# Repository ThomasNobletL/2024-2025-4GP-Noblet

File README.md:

<h1 align = "center"> Projet Capteur Graphite 4A - GP <h1> 
<h2 align="center"> Par NOBLET Thomas </h2>
<h3 align="center"> INSA de Toulouse, département Génie Physique, année 2024 - 2025 </h3>
  
<p align="center">
  
</p>

## <h2 align = "center"> Mesure de contrainte sous arduino & python d'un capteur graphite <h1>

### 1. Description

*Contexte*

Le projet consiste à reproduire une technologie low-tech de capteur de flexion en graphite, se basant sur l'article "Pencil Drawn Strain Gauges and Chemiresistors on Paper" de Cheng-Wei Lin, Zhibo Zhao, Jaemyung Kim & Jiaxing Huang.

*Principe*

Des traces de crayons sur du papier se comportent comme des résistances dont la valeur varie en fonction de la courbure du papier sur lequel elles sont dessinées. 

*Contenu du projet*

Une [datasheet du capteur](05_DataSheet/Graphite_Sensor_DATA_SHEET.pdf) a pu être réalisée à l'aide d'une carte Arduino Uno, d'un circuit d'amplification (dont le PCB a été réalisé sur KICAD) et d'une interface python.

***Matériel utilisé (non exhaustif)***
- **Capteur de contrainte en graphite** : Mine HB conseillée
- **LTC1050** : Amplificateur du circuit 
- **MCP 41050** : Permet de faire varier le gain du circuit d'amplification
- **Module Bluetooth HC-05** : Récupérer les données en Bluetooth  
- **Ecran OLED SS1306 en I2C** : Affichage des données sur le PCB

### 2. Circuit d'amplification & PCB

Le circuit d'amplification utilise un amplificateur LTC1050 avec un gain de R2/R1. La résistance R1 est un potentiomètre MCP41050 (de 125Ω à 50kΩ) donnant une plage de gain de 2 à 800.

<p align="center"><em>Figure 1 : Schéma Amplification </em></p>

<p align="center"><em>Figure 2 : Circuit réel </em></p>

Le PCB utilisé est celui-ci, avec les pins Rx et Tx de l'arduino connectées au HC05 (PCB Incorrect). Cette configuration est utilisable si on souhaite uploader le code arduino directement en bluetooth, mais il faut impérativement utiliser les pins 2 et 3 pour un upload depuis le port USB. Les pins 0 et 1 sont également utilisées par la liaison série vers un PC, ce qui provoque des erreurs en utilisant la connexion bluetooth sur ce port.

<p align="center"><em>Figure 3 : PCB Incorrect </em></p>

En l'occurence, aucun des codes python et arduino fournis fonctionnera durablement avec le premier PCB (30s), une erreurs série arrivera relativement rapidement, le PCB a donc été modifié à l'aide de câble pour correspondre à ce nouveau PCB. 

<p align="center"><em>Figure 4 : PCB Corrigé</em></p>

### 3. Interface & code Python 

L'architecture du code est décrite si dessous. La valeur de la résistance ainsi que l'affichage des mesures se fait directement depuis l'interface Qt, qui communique avec un thread gérant l'acquisition et l'envoie de données vers l'arduino qui les réceptionnes. Le code fonctionne à la fois en liaison série et bluetooth, il suffit de choisir depuis "Port choice".

Une valeur du gain observé est affichée dans l'interface, mais ne permet que d'obtenir un ordre de grandeur, la sensibilité des mesures sur l'arduino étant de 4,88 mV et le signal d'entrée trop faible (d'où l'intérêt du circuit d'amplification).

<p align="center"><em>Figure 5 : Architecture du code</em></p>

<p align="center"><em>Figure 5 : Interface Qt</em></p>

Le "run" permet de lancer le stockage des données reçues, mais écrase la précédente série réalisée, il faut donc sauvegarder directement après la fin de l'acquisition si le but est de prendre plusieurs séries d'affilée. 

### 4. Résultats

Les mesures ont été effectuées à l'aide de cylindres de diamètre **D** de **2, 2.5, 3, 3.5, 4, 4.5 et 5 cm** ainsi que de crayons de mines HB, 2B et 4B.
Avec la déformation $\epsilon$ = e/D, e étant l'épaisseur du papier (0,1 mm).

<p align="center"><em>Graphique 1 : Réponse en compression</em></p>

<p align="center"><em>Graphique 2 : Réponse en détente</em></p>

On remarque que la variation de résistance en compression et en détente est plus importante pour une mine moyennement dure et grasse (HB) que pour des mines plus grasses (2B, 4B).

<p align="center"><em>Graphique 3 : Comparaison avec un Flex sensor  </em></p>

En comparant avec un flex sensor de Spectra Symbol, on remarque que la réponse en détente est assez cohérente avec celle du capteur en graphite produit (le flex sensor de Spectra Symbol ne permet pas de comparer en compression, [Datasheet](06_Other/FLEX_SENSOR_-_SPECIAL_EDITION_DATA_SHEET.pdf)). De plus, les mesures on étés prises sans utiliser le circuit d'amplification. 

### 5. Limites et perspectives

*Le Bluetooth du HC-05*

  La connexion entre le module HC-05 et un PC est **trop instable** pour utiliser seulement l'interface python fournie **sur Mac OS**, l'appairage échoue souvent ou se coupe régulièrement. Il est préférable d'utiliser une connexion avec un port série. 
  
*Utilisation d'un module Wifi ESP32*

  Remplacer le HC-O5 par un module Wifi ESP32 pourrait permettre de se connecter plus aisément avec les OS Mac sur un même réseau et également en bluetooth.

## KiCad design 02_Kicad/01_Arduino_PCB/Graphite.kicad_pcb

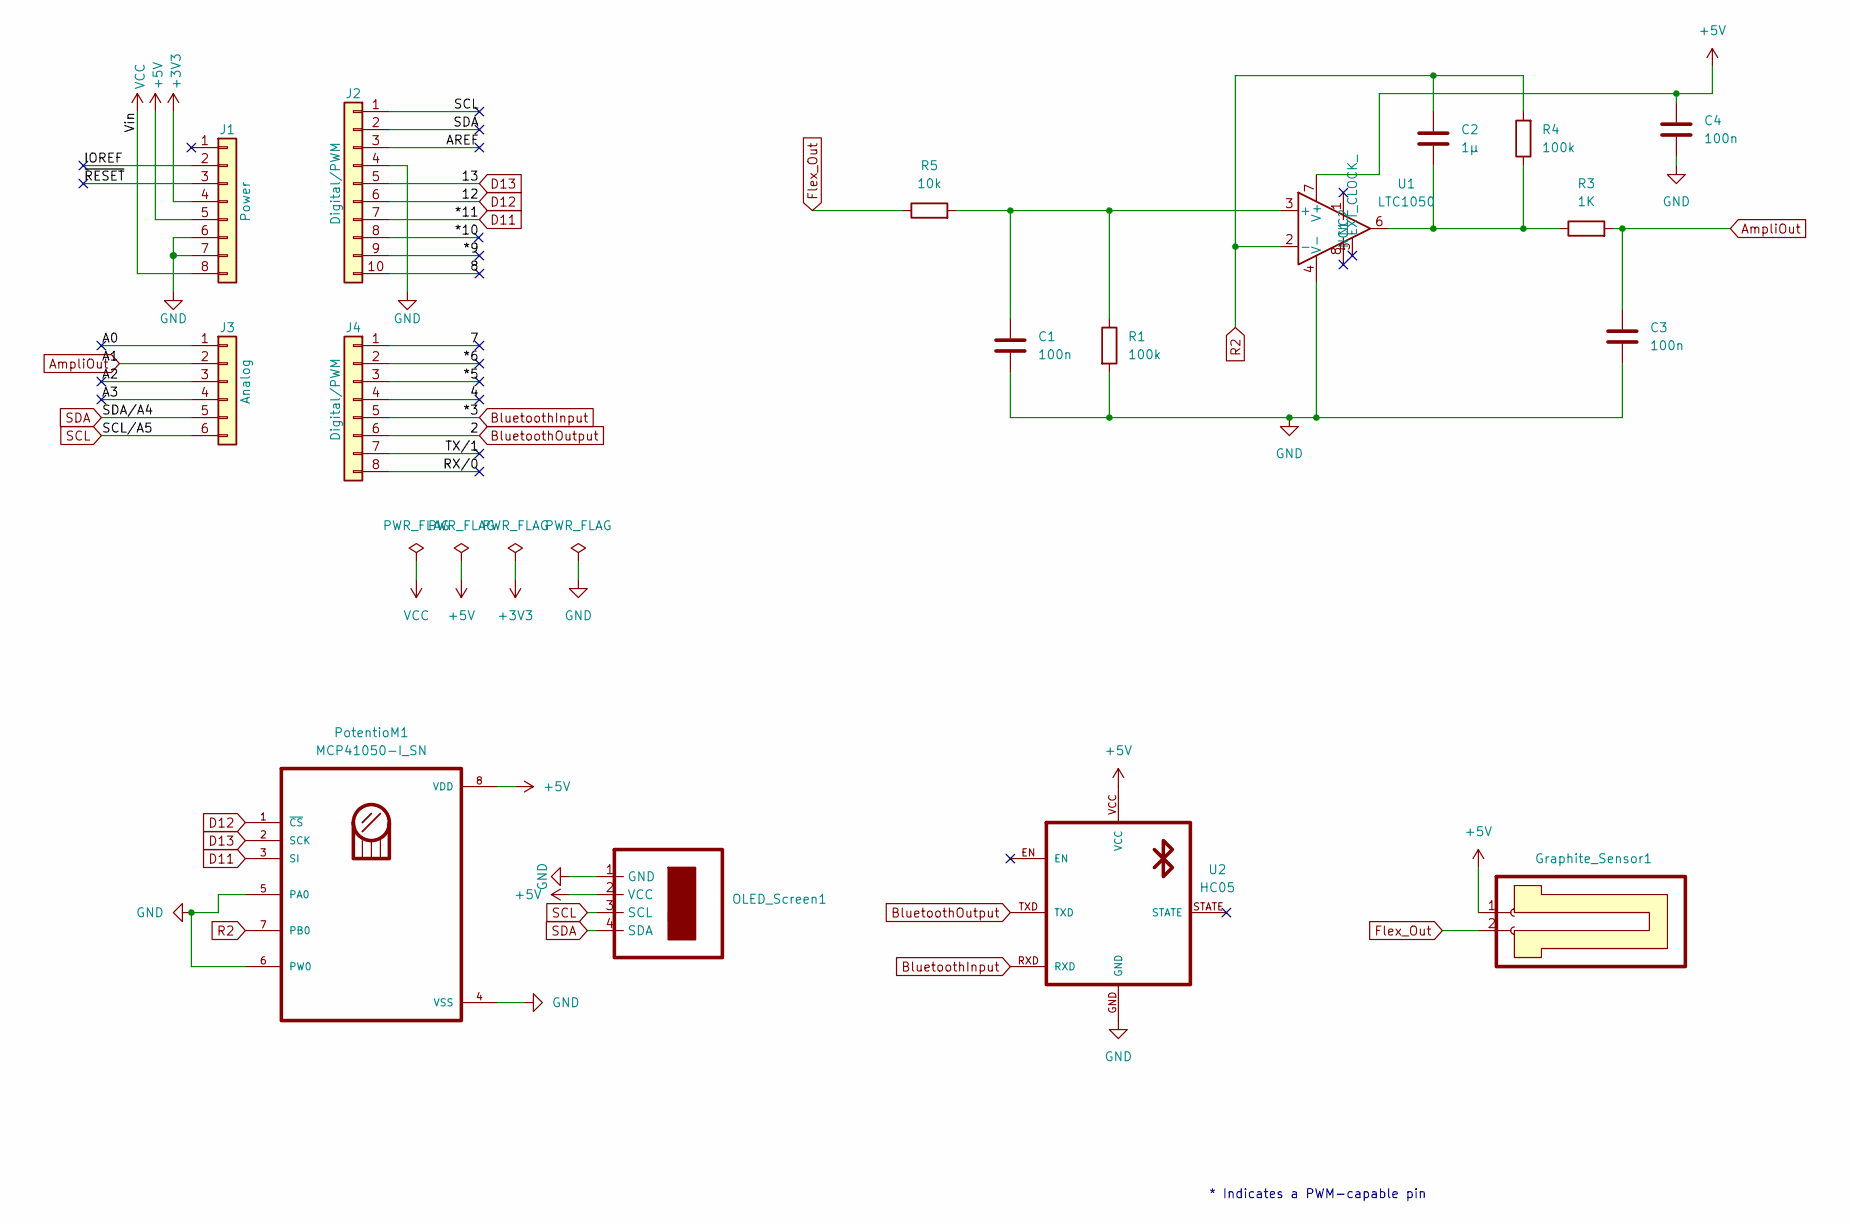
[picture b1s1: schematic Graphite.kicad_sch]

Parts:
C1, C3, C4: 100n; C_Disc_D3.0mm_W2.0mm_P2.50mm
C2: 1µ; C_Rect_L7.0mm_W4.5mm_P5.00mm
Graphite_Sensor1: Sensor
J1: Power; PinSocket_1x08_P2.54mm_Vertical
J2: Digital/PWM; PinSocket_1x10_P2.54mm_Vertical
J3: Analog; PinSocket_1x06_P2.54mm_Vertical
J4: Digital/PWM; PinSocket_1x08_P2.54mm_Vertical
OLED_Screen1: OLED
PotentioM1: MCP41050-I_SN; MCP41050
R1, R4: 100k; R_Axial_DIN0204_L3.6mm_D1.6mm_P7.62mm_Horizontal
R3: 1K; R_Axial_DIN0204_L3.6mm_D1.6mm_P7.62mm_Horizontal
R5: 10k; R_Axial_DIN0204_L3.6mm_D1.6mm_P7.62mm_Horizontal
U1: LTC1050
U2: HC05; HCO5

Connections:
+3V3: J1.4
+5V: C4.2, Graphite_Sensor1.1 (VCC), J1.5, OLED_Screen1.2 (VCC), PotentioM1.8 (VDD), U1.7 (V+), U2.VCC
/4: J4.4
/7: J4.1
/8: J2.10
/*5: J4.3
/*6: J4.2
/*9: J2.9
/*10: J2.8
/A0: J3.1
/A2: J3.3
/A3: J3.4
/AREF: J2.3
/IOREF: J1.2
/RX/0: J4.8
/TX/1: J4.7
/~RESET: J1.3
AmpliOut: C3.2, J3.2, R3.2
BluetoothInput: J4.5, U2.RXD
BluetoothOutput: J4.6, U2.TXD
D11: J2.7, PotentioM1.3 (SI)
D12: J2.6, PotentioM1.1 (~CS)
D13: J2.5, PotentioM1.2 (SCK)
Flex_Out: Graphite_Sensor1.2 (OutPut), R5.1
GND: C1.2, C3.1, C4.1, J1.6, J1.7, J2.4, OLED_Screen1.1 (GND), PotentioM1.4 (VSS), PotentioM1.5 (PA0), PotentioM1.6 (PW0), R1.2, U1.4 (V-), U2.GND
unnamed: C2.2, R3.1, R4.1, U1.6
unnamed: C1.1, R1.1, R5.2, U1.3 (+)
R2: C2.1, PotentioM1.7 (PB0), R4.2, U1.2 (-)
SCL: J2.1, J3.6, OLED_Screen1.3 (SCL)
SDA: J2.2, J3.5, OLED_Screen1.4 (SDA)
VCC: J1.8

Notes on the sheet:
* Indicates a PWM-capable pin

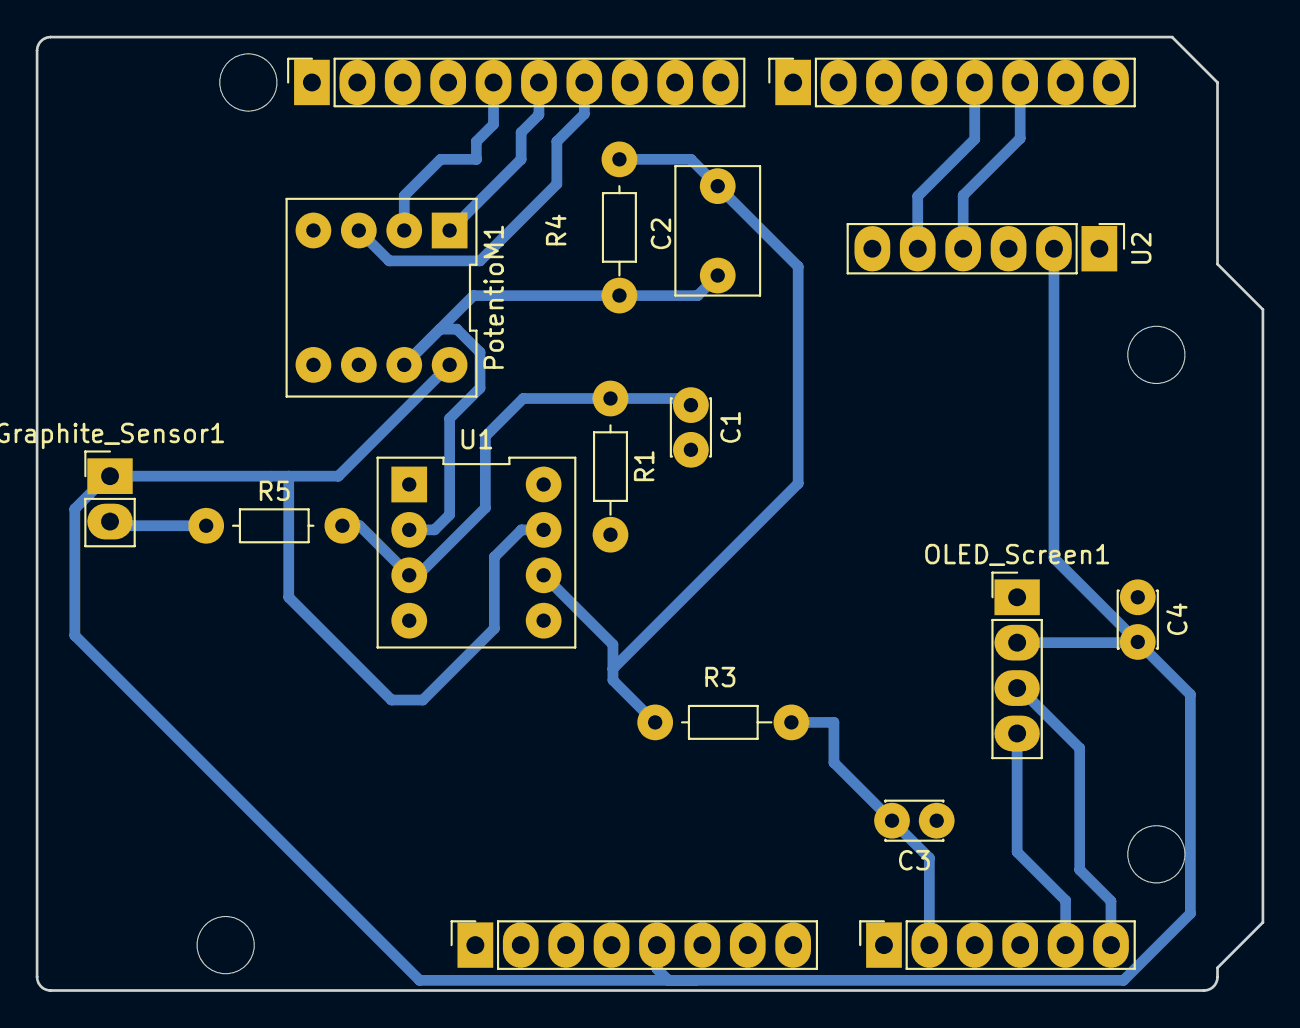
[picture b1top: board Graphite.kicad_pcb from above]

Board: 2 copper layers, 68.6 x 53.3 mm, 21 parts (0 on the bottom side), 14 nets.

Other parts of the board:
MH1, MH2, MH3, MH4: MountingHole_3.2mm

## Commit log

2025-05-19 Ajout dossiers precedents
2025-05-19 Rectification Kicad
2025-05-19 Ajouter MCP41050 resistances
2025-05-20 Code Arduino LCD
2025-05-21 Ajouter code final Python
2025-05-21 Reorganisation fichiers
2025-05-21 Create README.md
    Création du readme
2025-05-21 Update README.md
    Ajout description
2025-05-22 Update README.md
    Ajouts du Texte sans images
2025-05-22 ajout images
2025-05-22 correction !=0 sensor
2025-05-23 Gain code correction
2025-05-29 synchronisation git pc
2025-05-29 Ajout Nouvelles mesures
2025-05-29 Ajout Datasheet new
2025-05-29 Ajout screen interface
2025-05-29 Ajout docstring python
2025-05-29 modifications readme
2025-05-29 modification readme
2025-05-29 modification du readme
2025-05-29 modification schemas
2025-05-29 modification github
2025-05-29 PNG Courbes

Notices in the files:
README.md:
License: GPL v3
